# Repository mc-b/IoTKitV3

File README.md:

IoTKitV3
========

IoTKit V3 Board

- - -

Beispiele und Dokumentation zum IoTKit V3 Board. Für eine Einführung und Vertiefung in das Internet der Dinge siehe [Kurse und Weiterbildung auf Zertifikatsstufe CAS](#kurse-und-weiterbildung-auf-zertifikatsstufe-cas)

## Grundlagen

* [Hardware](hw/)
* [Software und Installation](sw/)
* [Kleine C/C++ Einführung](ccpp/)
* [GPIO](gpio/)
* [Das Konfigurationssystem (GPIO Belegungen)](config/)
* [Sensoren](sensors/)
* [Aktoren](actors/)

## Bus Systeme

* [UART](uart/)
* [I²C/TWI](i2c/)
* [SPI](spi/)

## WLAN (WiFi) / Bluetooth

* [WLAN (WiFi)](wlan/)
* [Bluetooth](bluetooth/)

### Internet IoT Protokolle

* [Sockets (TCP/UDP)](tcpip/)
* [HTTP](http/)
* [MQTT](mqtt/)
* [CoAP](coap/)

## Anwendungen

* [Cloud Dienste](cloud/) wie IFTTT, Yahoo Weather
* [LAM (Linux, Apache, MySQL) Server](LAM/)
* [Industrie V4.0](industrieV4/)
* [Roboter](roboter/)
* [NFC / RFID](rfid/)
* [Workflow](workflow/)
* [Edge Computing](edge/)
* [Built with Mbed](https://www.mbed.com/built-with-mbed/)

## Erweiterungen

Für die nachfolgenden Erweiterten Beispiele wird evtl. zusätzliche HW, wie z.B. ein Data Logging Shield, benötigt.

* [Speicher APIs](storage/)

## Kurse und Weiterbildung auf Zertifikatsstufe CAS

* [CAS Internet of Things (IoT) and Digital Ecosystem Technologien verstehen, Lösungen entwickeln](http://hslu.ch/casiot)
* [CAS Cloud and Platform Manager Mit Cloud-Expertise die Digitalisierung mitgestalten](http://hslu.ch/cascpm) 
* [Internet of Things (IoT) im Einsatz](https://www.digicomp.ch/d/IOTEIN)

## Links

* [ARM mbed](https://www.mbed.com)
* [Beispiele von Implementierungen mit mbed OS](https://www.mbed.com/built-with-mbed/)
* [mbed Labs](https://labs.mbed.com/)
* [ARM mbed YouTube Channel](https://www.youtube.com/channel/UCNcxd73dSceKtU77XWMOg8A)
* [Die drei Hauptklassen von IoT](https://www.arm.com/products/iot/soc)
* [Geschäftsmodelle und IoT](https://www.iot-lab.ch/publications/#whitepapers)
* [IoTKit Übersicht alle Versionen](https://github.com/mc-b/IoTKit#internet-der-dinge-kit)

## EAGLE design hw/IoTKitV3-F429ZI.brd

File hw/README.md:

## IoTKit V3
***

> [⇧ **Home**](../README.md)

Der Internet der Dinge Kit V3 besteht aus mehreren Boards, die mit den Beispielen verwendet werden können.

Es sind das 
* [IoTKitV3 K64F](#iotkitv3-k64f) - das eigens für das IoTKit entwickelte Board, basierend auf einen [NXP FRDM-K64F Board](https://os.mbed.com/platforms/FRDM-K64F/). 
* Ein [DISCO-L475VG-IOT01A](#DISCO-L475VG-IOT01A) Board mit einem zusätzlichen Shield, welches die fehlenden Treiber für Motoren etc. enthält.

Und zusätzliche [Komponenten](#zubehör) wie Motoren, LED Streifen, Sensoren etc.

Beide Boards können einzeln oder parallel verwendet werden.

## IoTKitV3 K64F
***

> [⇧ **Nach oben**](#)

Internet der Dinge Board

- - -

Der IoTKit ist ein [NXP FRDM-K64F Board](https://os.mbed.com/platforms/FRDM-K64F/) kompatibles Board.
 
Entstanden ist das Board durch die Kombination des [NXP FRDM-K64F Board](https://os.mbed.com/platforms/FRDM-K64F/) und einzelner Shields (z.B. Erweiterungsshield, Motorshield etc.). Dadurch sind Pin&#039;s doppelt belegt. Überall wo dies der Fall ist, kann immer nur eine Funktion gleichzeitig genutzt werden. Beispiel ist ein Gleichstrom Motor, am 2\. Anschluss angeschlossen, kann nicht gleichzeitig die MOSFET Verstärkerschaltung genutzt werden, weil sich diese die Pin&#039;s D5 - D7 teilen

* [Schaltplan](IoTKitV3.pdf) 

#### Board features

* [Bluetooth® V4.1 module (SPBTLE-RF)](../bluetooth/)
* [Proximity sensor, gesture and ambient light sensing (ALS) module (VL6180X)](../i2c#vl6180x)
* [low power, high sensitivity, RED, GREEN and BLUE color light sensor (RGB)](../i2c#ISL29125)
* [Hall Sensor](../sensors#Hall-Sensor)
* [NFC/RFID Reader](../rfid/)
* [Capacitive digital sensor for relative humidity and temperature (HTS221)](../i2c#hts221)
* [High-performance 3-axis magnetometer (LIS3MDL)](../i2c#lis3mdl)
* [3D accelerometer and 3D gyroscope (LSM6DSL)](../i2c#LSM6DSL)
* [Wi-Fi® module ESP8266](../wlan)

* OpenSDA USB Debug and Programming adapter
* Reset Button
* [SPI Header](../spi/)
* [GND/5V/Signal Arduino Pins D13 - D2](../gpio/)
* [I2C Header](../i2c/)
* [MOSFet](../actors)
* Expansion connectors: Arduino™ Uno V3
* [SWDAP](https://os.mbed.com/teams/mbed/wiki/SWDAP)
* [ARM Cortex M4 K64F MCU](https://www.nxp.com/products/processors-and-microcontrollers/arm-based-processors-and-mcus/kinetis-cortex-m-mcus/k-seriesperformancem4/k6x-ethernet/kinetis-k64-120-mhz-256kb-sram-microcontrollers-mcus-based-on-arm-cortex-m4-core:K64_120)
* [Grove Header](http://wiki.seeedstudio.com/Grove_System/)
* OLED Display
* [4 LED an GPIO D10 - D13](../gpio#DigitalOut)

* [H-Bridge](../actors/)
* [Buzzer](../gpio/)
* [Stepper Driver](../actors/)

* 12 Volt Power Supply
* Charger 5V from batt.
* [GND/5V/Signal Arduino Pins A0 - A5](../gpio/)
* [UART Header](../uart/)

* [Encoder Switch](../gpio)

## DISCO-L475VG-IOT01A
***

> [⇧ **Nach oben**](#)

Der Internet der Dinge Kit V3 Disco besteht aus den nachfolgenden Komponenten.

### Board DISCO-L475VG-IOT01A

Internet der Dinge Disco L475VG Board

- - -

* [mbed Page](https://os.mbed.com/platforms/ST-Discovery-L475E-IOT01A/)
* [Product Page](https://www.st.com/en/evaluation-tools/b-l475e-iot01a.html?icmp=tt5071_gl_bn_apr2017)
* [User Manual](https://www.st.com/content/ccc/resource/technical/document/user_manual/group0/b1/b8/7a/f2/f7/8d/4b/6b/DM00347848/files/DM00347848.pdf/jcr:content/translations/en.DM00347848.pdf)
* [Schematics](https://www.st.com/resource/en/schematic_pack/b-l475e-iot01ax_sch.zip)

#### Board features

* 64-Mbit Quad-SPI (Macronix) Flash memory
* Bluetooth® V4.1 module (SPBTLE-RF)
* Sub-GHz (868 or 915 MHz) low-power-programmable RF module (SPSGRF-868 or SPSGRF-915)
* [Wi-Fi® module Inventek ISM43362-M3G-L44 (802.11 b/g/n compliant)](../wlan)
* Dynamic NFC tag based on M24SR with its printed NFC antenna
* 2 digital omnidirectional microphones (MP34DT01)
* [Capacitive digital sensor for relative humidity and temperature (HTS221)](../i2c#HTS221)
* [High-performance 3-axis magnetometer (LIS3MDL)](../i2c#LIS3MDL)
* [3D accelerometer and 3D gyroscope (LSM6DSL)](../i2c#LSM6DSL)
* 260-1260 hPa absolute digital output barometer (LPS22HB)
* [Time-of-Flight and gesture-detection sensor (VL53L0X)](../i2c#VL53L0X)
* [2 push-buttons (user and reset)](../gpio)
* USB OTG FS with Micro-AB connector
* Expansion connectors:
* Arduino™ Uno V3
* PMOD

## NUCLEO-F303RE
***

Internet der Dinge Board Nucleo F303 RE
- - -

Das STM32 Nucleo-Board bietet Anwendern eine erschwingliche und flexible Möglichkeit, neue Ideen auszuprobieren und Prototypen zu bauen.

#### Board features

STM32F303RET6 in LQFP64 package
ARM®32-bit Cortex®-M4 CPU, 72 MHz max CPU frequency
512 KB Flash, 80 KB SRAM
GPIO (51) with external interrupt capability, 12-bit ADC (4), 12-bit DAC (2)
RTC, Timers (10)
I2C (3), USART (5), SPI (4), USB 2.0 full-speed, CAN

* [mbed Page](https://os.mbed.com/platforms/ST-Nucleo-F303RE/)

## Shield
***

Internet der Dinge Shield 

- - -

Der IoTKit V3 Shield ist ein Arduino Header kompatibler Shield.

Shield features
* 1 x SPI Header
* 1 x NFC/RFID Reader Header
* 2 x UART Header (1x Grove)
* 4 x Servo 4x3 Header
* 2 x I2C Header (1x Grove)
* 1 x Leistungsstufe für Schrittmotoren, Türöffner oder für die Ansteuerung von LED Streifen
* 1 x Hall Sensor
* 1 x OLED (128x64 Pixel)
* 1 x H-Bridge für 2 DC Motoren
* 8 x Analog/Digital 6x3 Header und 2 x Grove
* 1 x Buzzer

## Shield (small)

Internet der Dinge Shield (small)

- - -

Der IoTKit V3 Shield (small) ist die abgespeckte Variante des IoTKit Shields. 

Shield features
* 1 x SPI Header
* 1 x NFC/RFID Reader Header
* 1 x I2C Header (Grove)
* 1 x SD Card Header
* 1 x Hall Sensor
* 1 x OLED (128x64 Pixel)
* 1 x H-Bridge für 2 DC Motoren
* 4 x Analog/Digital 6x3 Header z.B. für Sensoren und Servos
* 1 x Grove
* 1 x Anschluss für BMP180 Sensor für die Messung von Luftdruck und Temperatur.
* 1 x Anschluss für APDS-9930 ein Umgebungslicht (ALS) und Näherungssensor

## Zubehör
***

> [⇧ **Nach oben**](#)

*   **Sensoren** RFID Reader (MFRC-522), PIR Sensor (SR501), Ultrasonic Wave Detector Ranging Module (HC-SR04), Digital Temperature and Humidity Sensor (DHT11), Microswitch Limit Switch: [AliExpress](http://www.aliexpress.com/), [EBay](http://www.ebay.ch/), [Conrad](http://www.conrad.ch/) (teilweise)
*   **Aktoren** 5V Stepper Motor (28BYJ-48), DC Motor, Wheels, 9g Mini Micro Servo (SG90): [AliExpress](http://www.aliexpress.com/), [EBay](http://www.ebay.ch/), [Conrad](http://www.conrad.ch/) (teilweise)
*   **LED Strip&#039;s, Matrix** Led Pixel Strip (WS2801 - Variante mit 4 Adern beachten!), Dot LED Matrix: [AliExpress](http://www.aliexpress.com/), [EBay](http://www.ebay.ch/)
*   **Modems** USB To RS232 TTL Konverterkabel: [AliExpress](http://www.aliexpress.com/), [EBay](http://www.ebay.ch/)
*   **IC&#039;s, Transistoren, Widerstände, Kabel, Stecker (Crimp) etc.** [http://www.distrelec.ch/](http://www.distrelec.ch/), [https://www.reichelt.de/](https://www.reichelt.de/), [Pusterla (Ladengeschäft in Zürich)](http://www.pusterla.ch/)

Die restlichen Teile zum Drucken, mittels 3D Drucker, sind auf [http://www.thingiverse.com/](http://www.thingiverse.com/thing:805047) zu finden. Dort befindet sich auch die Dateien um die IoTKit Box, mittels einer CNC Maschine, zu fräsen. Zum Befestigen der Teile werden 2 x M3x20 Linsenschrauben mit Muttern (Schrittmotor ), 1 x M3x30 Linsenschraube mit Mutter (Motorklammer) und zwei Drahtstife (Nägel) mit Durchmesser 1.5mm o.ä. für den Endschalter benötigt.

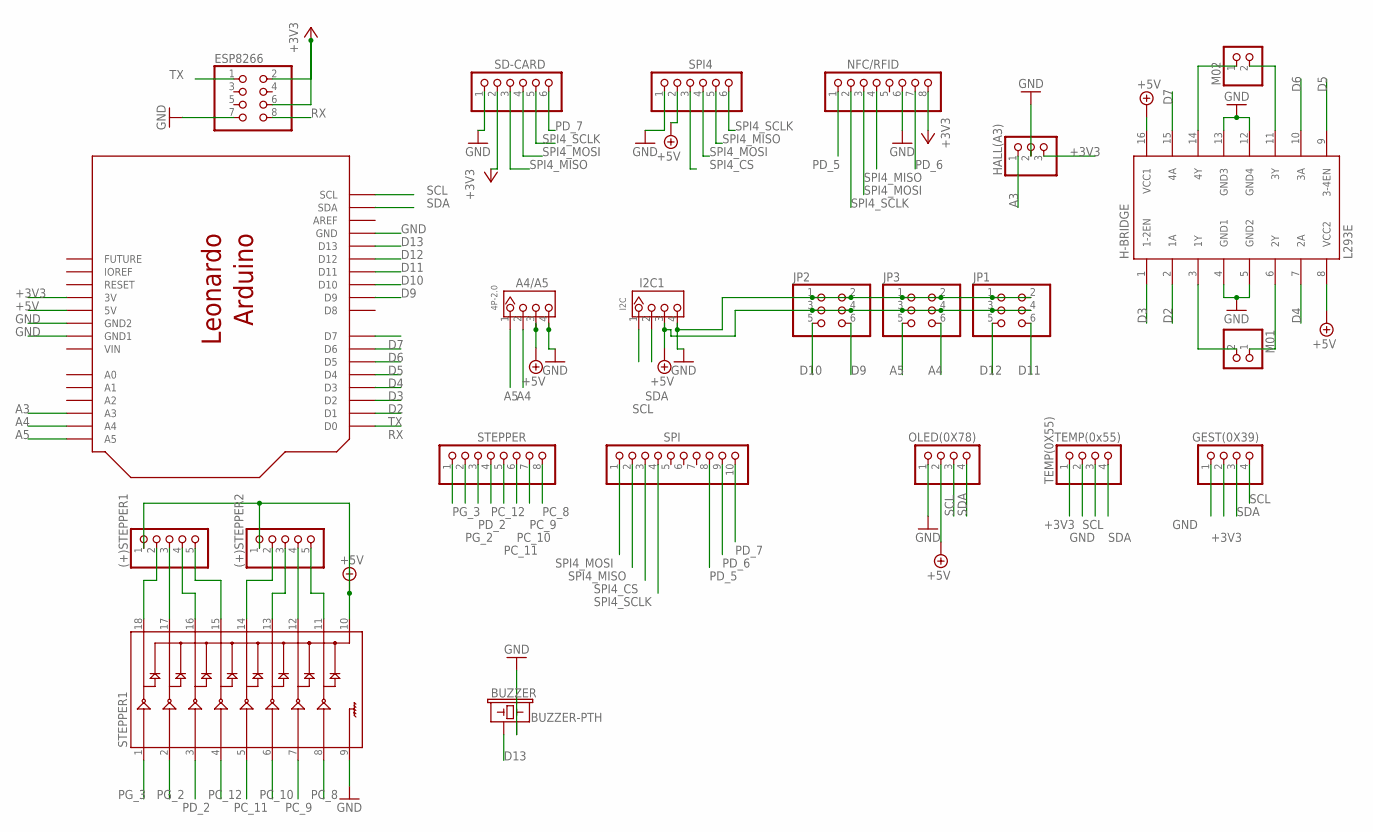
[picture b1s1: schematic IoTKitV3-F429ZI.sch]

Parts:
(+)STEPPER1, (+)STEPPER2: PINHD-1X5; 1X05
A4/A5: 4P-2.0; HW4-2.0
BUZZER: BUZZER-PTH; BUZZER-12MM
ESP8266: PINHD-2X4; 2X04
GEST(0X39): PINHD-1X4; 1X04
H-BRIDGE: L293E; DIL16
HALL(A3): PINHD-1X3; 1X03
I2C1: I2C; HW4-2.0
JP1, JP2, JP3: PINHD-2X3; 2X03
M01, M02: PINHD-1X2; 1X02
NFC/RFID: PINHD-1X8; 1X08
OLED(0X78): PINHD-1X4; 1X04
SD-CARD: PINHD-1X6; 1X06
SPI: PINHD-1X10; 1X10
SPI4: PINHD-1X6; 1X06
STEPPER: PINHD-1X8; 1X08
STEPPER1: ULN2803DIP; DIL18
TEMP(0X55): TEMP(0x55); 1X04
U$1: ARDUINO_LEONARDO

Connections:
+3V3: ESP8266.2, ESP8266.6, GEST(0X39).2, HALL(A3).3, NFC/RFID.8, SD-CARD.2, TEMP(0X55).1, U$1.3V
+5V: (+)STEPPER1.1, (+)STEPPER2.1, A4/A5.3, H-BRIDGE.8 (VCC2), H-BRIDGE.16 (VCC1), I2C1.3, JP1.3, JP1.4, JP2.3, JP2.4, JP3.3, JP3.4, OLED(0X78).2, SPI4.2, STEPPER1.10, U$1.5V
A3: HALL(A3).1, U$1.A3
A4: A4/A5.2, JP3.6, U$1.A4
A5: A4/A5.1, JP3.5, U$1.A5
D2: H-BRIDGE.2 (1A), U$1.D2
D3: H-BRIDGE.1 (1-2EN), U$1.D3
D4: H-BRIDGE.7 (2A), U$1.D4
D5: H-BRIDGE.9 (3-4EN), U$1.D5
D6: H-BRIDGE.10 (3A), U$1.D6
D7: H-BRIDGE.15 (4A), U$1.D7
D9: JP2.6, U$1.D9
D10: JP2.5, U$1.D10
D11: JP1.6, U$1.D11
D12: JP1.5, U$1.D12
D13: BUZZER.+ (1), U$1.D13
GND: A4/A5.4, BUZZER.- (2), ESP8266.7, GEST(0X39).1, H-BRIDGE.4 (GND1), H-BRIDGE.5 (GND2), H-BRIDGE.12 (GND4), H-BRIDGE.13 (GND3), HALL(A3).2, I2C1.4, JP1.1, JP1.2, JP2.1, JP2.2, JP3.1, JP3.2, NFC/RFID.6, OLED(0X78).1, SD-CARD.1, SPI4.1, STEPPER1.9, TEMP(0X55).2, U$1.GND, U$1.GND$2 (GND2), U$1.GND$3 (GND1)
M01: H-BRIDGE.6 (2Y), M01.1
unnamed: (+)STEPPER2.2, STEPPER1.14
unnamed: (+)STEPPER2.3, STEPPER1.13
unnamed: (+)STEPPER2.4, STEPPER1.12
unnamed: (+)STEPPER2.5, STEPPER1.11
unnamed: (+)STEPPER1.2, STEPPER1.18
unnamed: (+)STEPPER1.3, STEPPER1.17
unnamed: (+)STEPPER1.4, STEPPER1.16
unnamed: (+)STEPPER1.5, STEPPER1.15
unnamed: H-BRIDGE.14 (4Y), M02.1
unnamed: H-BRIDGE.11 (3Y), M02.2
unnamed: H-BRIDGE.3 (1Y), M01.2
PC_8: STEPPER.8, STEPPER1.8
PC_9: STEPPER.7, STEPPER1.7
PC_10: STEPPER.6, STEPPER1.6
PC_11: STEPPER.5, STEPPER1.5
PC_12: STEPPER.4, STEPPER1.4
PD_2: STEPPER.3, STEPPER1.3
PD_5: NFC/RFID.1, SPI.8
PD_6: NFC/RFID.7, SPI.9
PD_7: SD-CARD.6, SPI.10
PG_2: STEPPER.2, STEPPER1.2
PG_3: STEPPER.1, STEPPER1.1
RX: ESP8266.8, U$1.D0
SCL: GEST(0X39).4, I2C1.1, OLED(0X78).3, TEMP(0X55).3, U$1.SCL
SDA: GEST(0X39).3, I2C1.2, OLED(0X78).4, TEMP(0X55).4, U$1.SDA
SPI4_CS: SPI.3, SPI4.3
SPI4_MISO: NFC/RFID.4, SD-CARD.3, SPI.2, SPI4.5
SPI4_MOSI: NFC/RFID.3, SD-CARD.4, SPI.1, SPI4.4
SPI4_SCLK: NFC/RFID.2, SD-CARD.5, SPI.4, SPI4.6
TX: ESP8266.1, U$1.D1
VIN: U$1.VIN

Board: 2 copper layers, 23 parts (0 on the bottom side), 48 nets, no tracks yet.

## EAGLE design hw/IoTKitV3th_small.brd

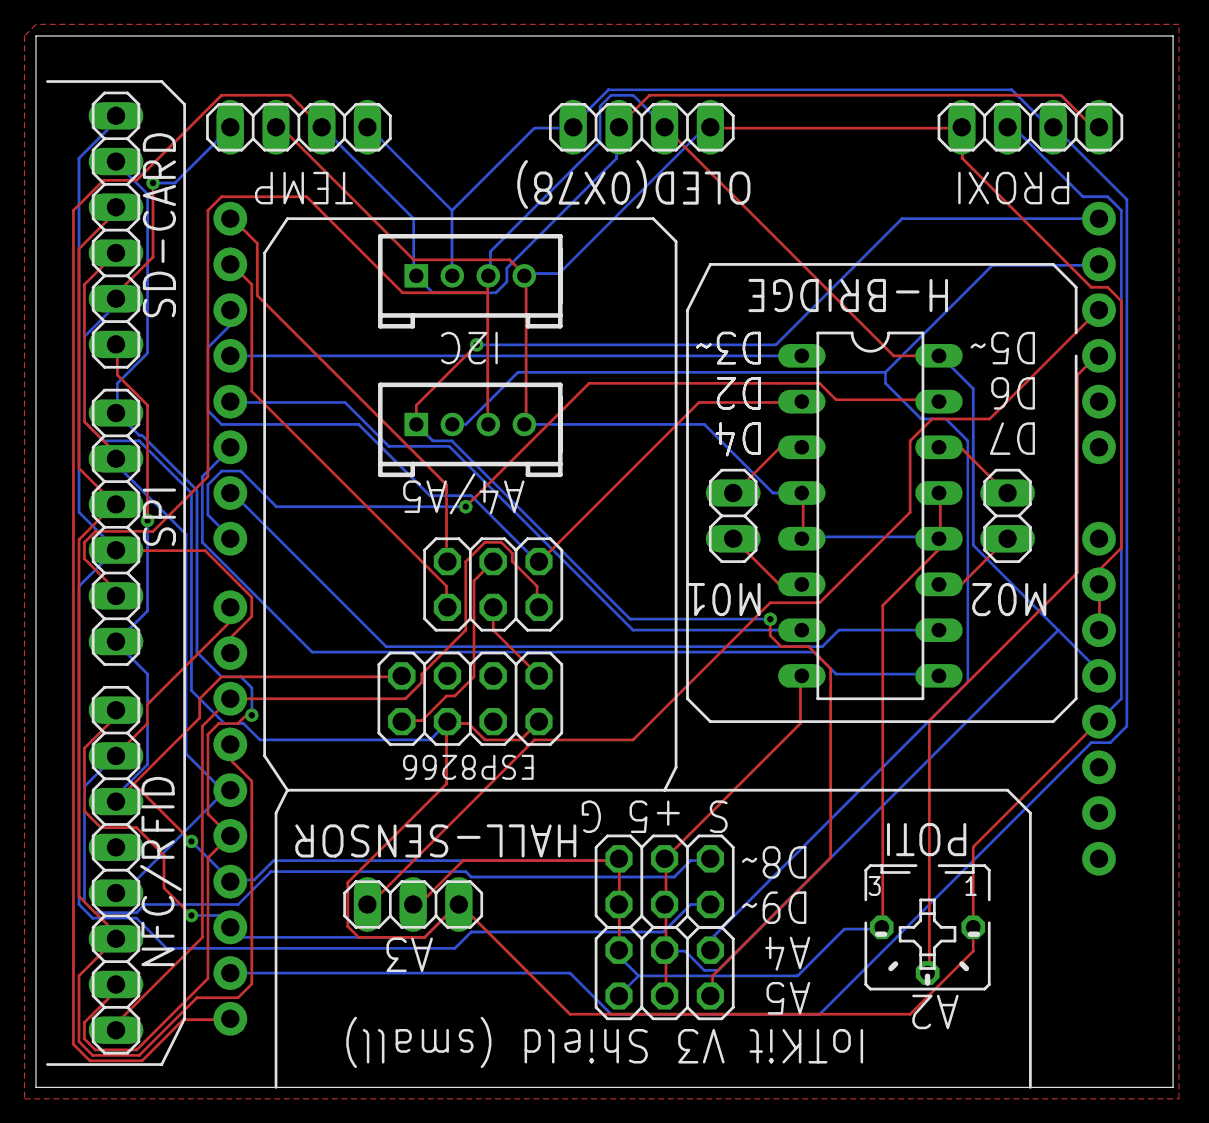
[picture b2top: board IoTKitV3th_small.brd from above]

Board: 2 copper layers, 63.2 x 58.4 mm, 18 parts (0 on the bottom side), 29 nets.

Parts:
B1: ARDUINO_UNO_R3_SHIELDNOLABELS; UNO_R3_SHIELD_NOLABELS
ESP8266: 2X04
H-BRIDGE: L293E; DIL16
HALL-SENSOR: 1X03
I2C: 4P-2.0; HW4-2.0
I2C1: I2C; HW4-2.0
JP1, JP2, JP3: 2X03
M01, M02: 1X02
NFC/RFID: 1X08
OLED(0X78): 1X04
POTI: B25P
PROXI: 1X04
SD-CARD: 1X06
SPI: 1X06
TEMP: TEMP; 1X04

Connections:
+3V3: B1.3.3V, B1.AREF, ESP8266.2, ESP8266.6, HALL-SENSOR.3, NFC/RFID.8, POTI.A, PROXI.2, SD-CARD.2, TEMP.1
+5V: B1.5V, H-BRIDGE.8, H-BRIDGE.16, I2C.3, I2C1.3, JP2.3, JP2.4, JP3.3, JP3.4, OLED(0X78).2, SPI.2
A2: B1.A2, POTI.S
A3: B1.A3, HALL-SENSOR.1
A4: B1.A4, I2C.2, JP3.6
A5: B1.A5, I2C.1, JP3.5
D2: B1.D2, H-BRIDGE.2, JP1.6
D3: B1.D3, H-BRIDGE.1
D4: B1.D4, H-BRIDGE.7
D5: B1.D5, H-BRIDGE.9
D6: B1.D6, H-BRIDGE.10
D7: B1.D7, H-BRIDGE.15
D8: B1.D8, JP2.6, NFC/RFID.7
D9: B1.D9, JP2.5, SD-CARD.6, SPI.3
D10: B1.D10, JP1.5, NFC/RFID.1
D11: B1.D11, NFC/RFID.3, SD-CARD.4, SPI.4
D12: B1.D12, NFC/RFID.4, SD-CARD.3, SPI.5
D13: B1.D13, NFC/RFID.2, SD-CARD.5, SPI.6
GND: B1.GND@0, B1.GND@1, B1.GND@2, ESP8266.7, H-BRIDGE.4, H-BRIDGE.5, H-BRIDGE.12, H-BRIDGE.13, HALL-SENSOR.2, I2C.4, I2C1.4, JP2.1, JP2.2, JP3.1, JP3.2, NFC/RFID.6, OLED(0X78).1, POTI.E, PROXI.1, SD-CARD.1, SPI.1, TEMP.2
M01: H-BRIDGE.6, M01.1
unnamed: ESP8266.1, JP1.3
unnamed: ESP8266.8, JP1.4
unnamed: H-BRIDGE.14, M02.1
unnamed: H-BRIDGE.11, M02.2
unnamed: H-BRIDGE.3, M01.2
RX: B1.RX, JP1.2
SCL: B1.SCL, I2C1.1, OLED(0X78).3, PROXI.4, TEMP.3
SDA: B1.SDA, I2C1.2, OLED(0X78).4, PROXI.3, TEMP.4
TX: B1.TX, JP1.1

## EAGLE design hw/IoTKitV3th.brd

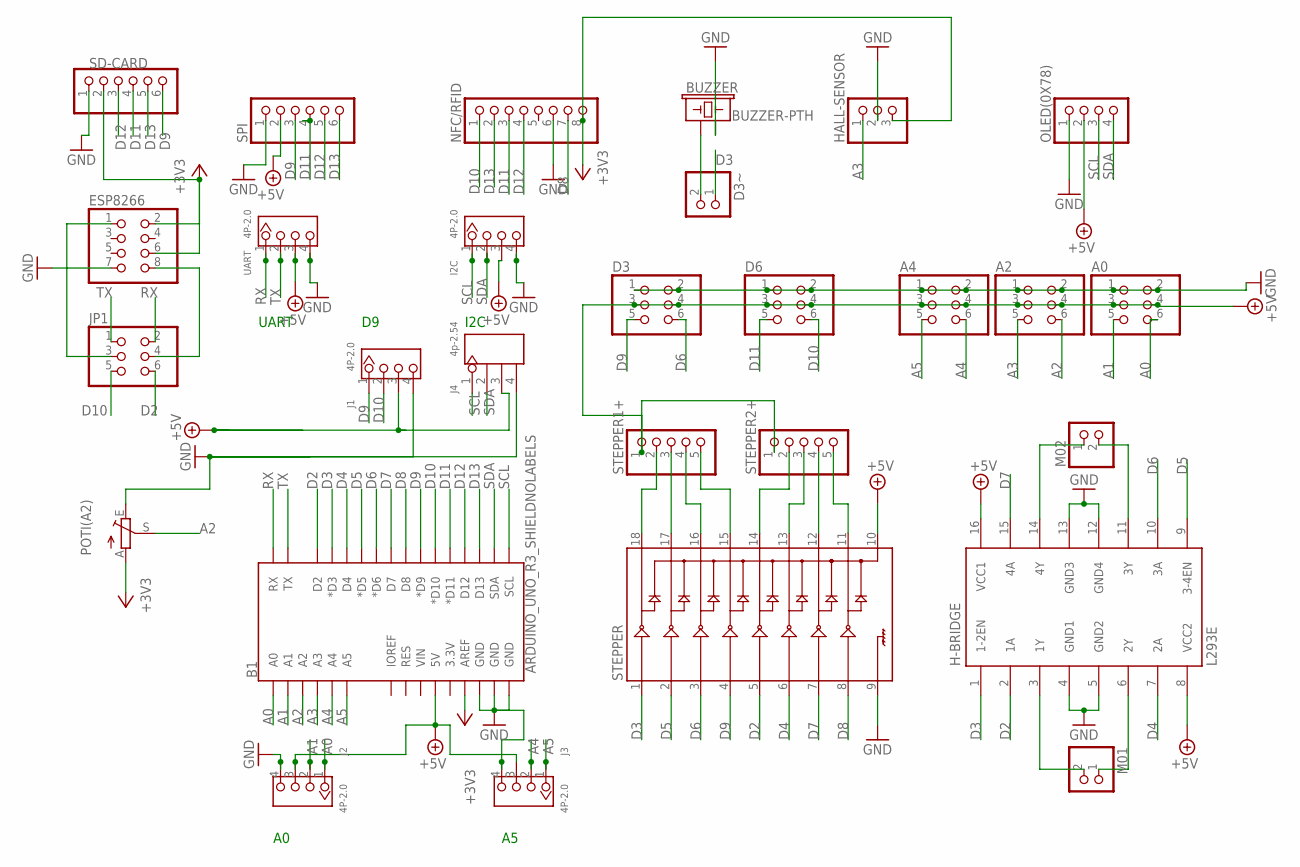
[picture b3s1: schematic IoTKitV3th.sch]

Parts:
A0, A2, A4: PINHD-2X3; 2X03
B1: ARDUINO_UNO_R3_SHIELDNOLABELS; UNO_R3_SHIELD_NOLABELS
BUZZER: BUZZER-PTH; BUZZER-12MM
D3, D6: PINHD-2X3; 2X03
D3~: PINHD-1X2; 1X02
ESP8266: PINHD-2X4; 2X04
H-BRIDGE: L293E; DIL16
HALL-SENSOR: PINHD-1X3; 1X03
I2C: 4P-2.0; HW4-2.0
J1, J2, J3: 4P-2.0; HW4-2.0
J4: 4p-2.54; H4-2.54
JP1: PINHD-2X3; 2X03
M01, M02: PINHD-1X2; 1X02
NFC/RFID: PINHD-1X8; 1X08
OLED(0X78): PINHD-1X4; 1X04
POTI(A2): TRIM_EU-B25P; B25P
SD-CARD: PINHD-1X6; 1X06
SPI: PINHD-1X6; 1X06
STEPPER: ULN2803DIP; DIL18
STEPPER1+, STEPPER2+: PINHD-1X5; 1X05
UART: 4P-2.0; HW4-2.0

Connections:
+3V3: B1.AREF, ESP8266.2, ESP8266.6, HALL-SENSOR.3, NFC/RFID.8, POTI(A2).A, SD-CARD.2
+5V: A0.3, A0.4, A2.3, A2.4, A4.3, A4.4, B1.5V, D3.3, D3.4, D6.3, D6.4, H-BRIDGE.8 (VCC2), H-BRIDGE.16 (VCC1), I2C.3, J1.3, J2.3, J3.3, J4.3, OLED(0X78).2, SPI.2, STEPPER.10, STEPPER1+.1, STEPPER2+.1, UART.3
A0: A0.6, B1.A0, J2.1
A1: A0.5, B1.A1, J2.2
A2: A2.6, B1.A2, POTI(A2).S
A3: A2.5, B1.A3, HALL-SENSOR.1
A4: A4.6, B1.A4, J3.2
A5: A4.5, B1.A5, J3.1
D2: B1.D2, H-BRIDGE.2 (1A), JP1.6, STEPPER.5
D3: B1.D3 (*D3), D3~.1, H-BRIDGE.1 (1-2EN), STEPPER.1
D4: B1.D4, H-BRIDGE.7 (2A), STEPPER.6
D5: B1.D5 (*D5), H-BRIDGE.9 (3-4EN), STEPPER.2
D6: B1.D6 (*D6), D3.6, H-BRIDGE.10 (3A), STEPPER.3
D7: B1.D7, H-BRIDGE.15 (4A), STEPPER.7
D8: B1.D8, NFC/RFID.7, STEPPER.8
D9: B1.D9 (*D9), D3.5, J1.1, SD-CARD.6, SPI.3, STEPPER.4
D10: B1.D10 (*D10), D6.6, J1.2, JP1.5, NFC/RFID.1
D11: B1.D11 (*D11), D6.5, NFC/RFID.3, SD-CARD.4, SPI.4
D12: B1.D12, NFC/RFID.4, SD-CARD.3, SPI.5
D13: B1.D13, NFC/RFID.2, SD-CARD.5, SPI.6
GND: A0.1, A0.2, A2.1, A2.2, A4.1, A4.2, B1.GND@0 (GND), B1.GND@1 (GND), B1.GND@2 (GND), BUZZER.- (2), D3.1, D3.2, D6.1, D6.2, ESP8266.7, H-BRIDGE.4 (GND1), H-BRIDGE.5 (GND2), H-BRIDGE.12 (GND4), H-BRIDGE.13 (GND3), HALL-SENSOR.2, I2C.4, J1.4, J2.4, J3.4, J4.4, NFC/RFID.6, OLED(0X78).1, POTI(A2).E, SD-CARD.1, SPI.1, STEPPER.9, UART.4
M01: H-BRIDGE.6 (2Y), M01.1
unnamed: STEPPER.14, STEPPER2+.2
unnamed: STEPPER.13, STEPPER2+.3
unnamed: STEPPER.12, STEPPER2+.4
unnamed: STEPPER.11, STEPPER2+.5
unnamed: BUZZER.+ (1), D3~.2
unnamed: ESP8266.1, JP1.3
unnamed: ESP8266.8, JP1.4
unnamed: STEPPER.18, STEPPER1+.2
unnamed: STEPPER.17, STEPPER1+.3
unnamed: STEPPER.16, STEPPER1+.4
unnamed: STEPPER.15, STEPPER1+.5
unnamed: H-BRIDGE.14 (4Y), M02.1
unnamed: H-BRIDGE.11 (3Y), M02.2
unnamed: H-BRIDGE.3 (1Y), M01.2
RX: B1.RX, JP1.2, UART.1
SCL: B1.SCL, I2C.1, J4.1, OLED(0X78).3
SDA: B1.SDA, I2C.2, J4.2, OLED(0X78).4
TX: B1.TX, JP1.1, UART.2

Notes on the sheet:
UART
I2C

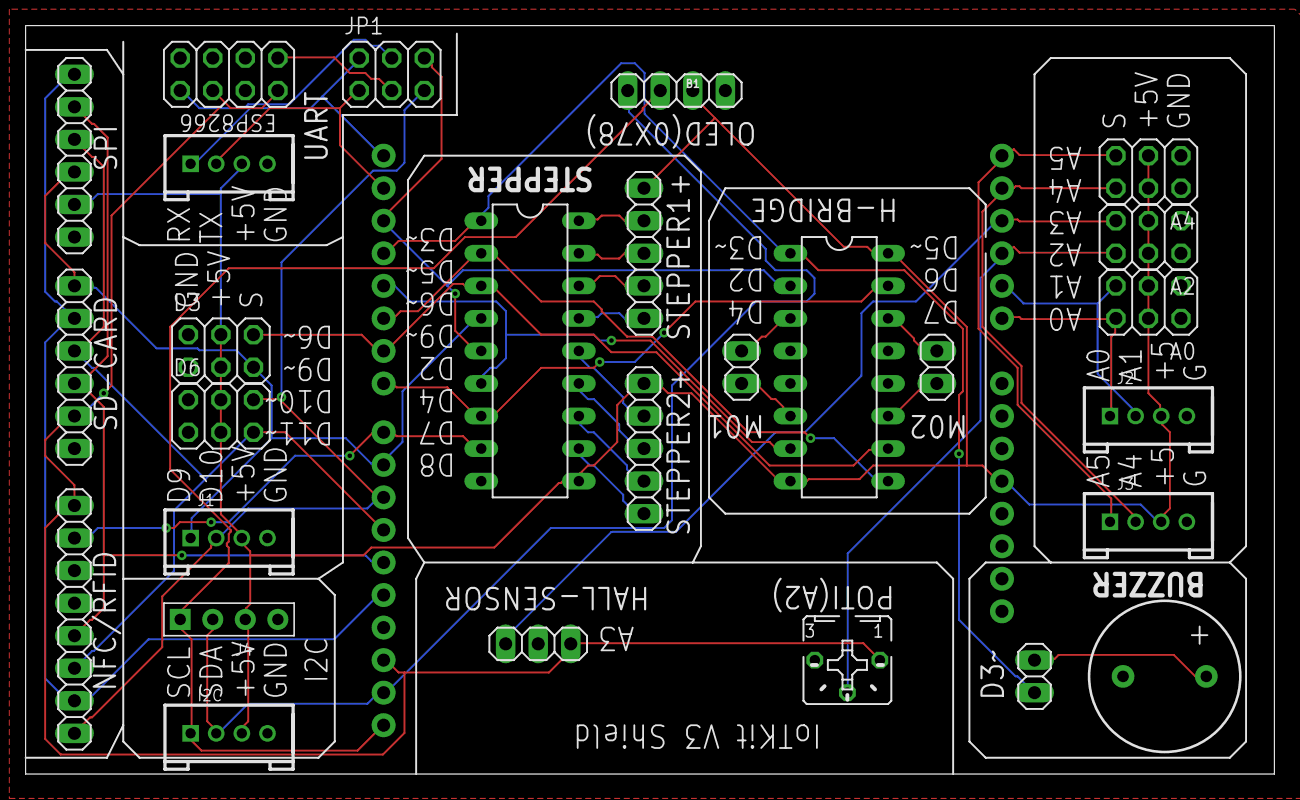
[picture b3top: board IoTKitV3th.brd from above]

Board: 2 copper layers, 97.5 x 58.4 mm, 28 parts (0 on the bottom side), 40 nets.

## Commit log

2017-08-30 Initial Commit - nicht angepasst an IoTKit V3
2017-08-30 D9 statt D7, weil D7 ein PWM Pin
2017-08-30 Umbau auf User-Button und LED1
2017-08-31 Angepasst an DISCO-L475VG-IOT
2017-08-31 Eclipse Dateien
2017-08-31 D1/D0 und USBTX/USBRX sind unterschiedliche Pin's
2017-08-31 Obsolet
2017-08-31 The BSP driver for the B-L475E-IOT01 board.
2017-08-31 Beispiel Magnetometer auf Board
2017-08-31 Link
2017-09-01 Magnetometer Beschreibung
2017-09-01 Umbau mbed OS V5.x
2018-09-08 Umgestellt auf FRMD K64F kompatibles Board
2018-09-08 Erweiterungen VSCode und PlatformIO
2018-09-08 Obsolet durch lernkube und duk
2018-09-08 Obsolet bzw. in mbed V5 nicht mehr unterstuetzt
2018-09-08 Umbau auf IoTKit V3
2018-09-08 SW Installation und Einsatz
2018-09-08 Doku
2018-09-08 Abgestimmt mit VSCode
2018-09-08 Libraries
2018-09-08 Khz Angabe
2018-09-08 Angepasst an IoTKit V3
2018-09-08 Update auf IoTKit V3
2018-09-09 Easy Connect Library
2018-09-09 RFID Library
2018-09-09 Wifi Beispiel
2018-09-09 MQTT
2018-09-09 no workspace
2018-10-04 Entwicklungsumgebungen
2018-10-04 Ueberarbeitet
2018-10-04 Ueberarbeitung
2018-10-04 BUILD ausschliessen
2018-10-04 Servo mbed OS V5 konform ansprechen
2018-10-04 Anpassen an mbed OS V5
2018-10-05 mbed OS V5
2018-10-05 mbed-cli Installation
2018-10-05 Display Test
2018-10-06 Update EPS8266 Beschreibung
2018-10-06 mbed?
2018-10-06 FAIL.TXT
2018-10-06 Board features
2018-10-06 Encoder Switch
2018-10-06 Links
2018-10-06 VL6180X
2018-10-06 ISL29125 - low power, high sensitivity, RED, GREEN and BLUE color light sensor
2018-10-06 HTS221
2018-10-06 LIS3MDL
2018-10-06 LSM6DSL
2018-10-06 NTP Beispiel
2018-10-07 HTTP Libraries und Beispiel
2018-10-07 IoTKit V3 Template
2018-10-07 PlatformIO entfernt, mbed OS Version ist zu alt
2018-10-07 CoAP Beispiel
2018-10-07 Umbau Bluetooth
2018-10-07 Einleitung
2018-11-14 C/C++ Einfuehrung
2018-11-16 Korrekturen
2018-11-28 printf, scanf Links
2018-12-04 Umbau mbed OS 5.10
2019-02-04 Mehr Kommentar
2019-02-04 Link Beispiel
2019-02-04 Kommentar ergaenzt
2019-02-04 Beschreibung
2019-02-05 Update mbed OS fuer WLAN
2019-02-12 IFTTT Beschreibung nachgefuehrt
2019-02-12 Built with Mbed
2019-02-18 ntp-client entfernt, gibt Probleme
2019-02-18 Link korr.
2019-02-18 Fehlerhafte Library entfernt
2019-02-25 Falsches Board
2019-02-25 Falscher Wertabfrage
2019-02-26 ThingSpeak Beispiel
2019-03-02 Mehr Beispiele portiert
2019-03-07 Angepasstes Beispiel an IoTKitV3
2019-03-15 Workflow Update auf neuste Beispiele
2019-03-20 Umstellung mbed OS5
2019-03-20 Bluetooth Beispiel inkl. Library
2019-03-21 Mehr Links
2019-03-23 mbed-cli Installation Ueberarbeitet
2019-03-23 Feintuning
2019-03-24 Beacon Beispiel
2019-03-27 Storage
2019-03-27 C++ Einstellungen fuer Eclipse inkl. GCC ARM Paths
2019-03-27 Buildet aktuelles Verzeichnis
2019-03-30 gibt Probleme beim compilieren. mbed_app.json aus template verwenden
2019-04-11 Link auf Beispielprogramm
2019-04-11 Ueberarbeitet und Erweitert um Button und Encoder Infos
2019-04-13 Falsches Format
2019-04-15 RFID Reader integriert
2019-04-17 6D Ausgabe
2019-04-17 Restliche Beispiele fuer Acc/Gyro
2019-04-17 Falscher Link
2019-04-20 Magnet und eCompass Abhandlung
2019-04-20 Typo
2019-04-21 Aufgeraeumt
2019-04-23 Umbau Symbolische Bezeichner - Doku kompakter
2019-04-23 Tabelle
2019-04-23 u.s.b.
2019-04-23 Beispiel AnalogIn
2019-04-23 Encoder
2019-04-23 Uebungen
2019-04-23 Abgleich
2019-04-23 Umbau auf Symbolische Bezeichner
2019-04-23 Doku ueberarbeitet
2019-04-23 Klarstellungen
2019-04-23 + 2 Uebungen
2019-04-23 Konfig
2019-04-23 Doku umbau
2019-04-23 Doku komprimiert
2019-04-23 Syntax
2019-04-23 SW Installation abgestimmt
2019-04-23 Serielle Kommunikation
2019-04-23 Kombination Boards
2019-04-24 Boards zusammengefasst
2019-04-24 Multi Board
2019-04-24 Multi Boards
2019-04-24 Umbau
2019-04-24 Doku Redesing
2019-04-24 Doku Redesign
2019-04-25 Neues Beispiel und Doku Redesign RFID
2019-04-25 Formatierung
2019-04-25 printf und scanf Beispiel
2019-04-25 NTP Online Beispiel
2019-04-25 Dokue Redesign
2019-04-25 Konfigurationssystem
2019-04-25 Ausgabe Details
2019-04-25 Home
2019-04-25 RFID und Encoder entfernt beim DISCO_L475VG_IOT01A, WLAN Modem haengt
2019-04-26 Temperatur Sensor Extern integriert
2019-04-26 Temperatur Sensor extern
2019-04-26 IoTKit Macros
2019-04-27 Feinschliff
2019-04-27 Link Kurse
2019-04-27 Einfuehrungsvideo
2019-04-30 Blog MQTT Library
2019-05-08 Doppelbelegung Disco Board von D3, Motor auf M02 verschoben
2019-05-12 Nucleo Board integriert in Build
2019-05-19 V1.1 inkl. SD Card, Poti, ESP8266, Schrift gekehrt
2019-05-19 Microbit - Arduino Adapter
2019-05-24 Unterstuetzung weitere Boards
2019-05-24 TARGET_NUCLEO_F746ZG
2019-05-25 XML Parser Library
2019-05-25 Fehlende Library und doppelte Globale Variable
2019-05-25 Unnoetige Variable
2019-05-25 Namenskonflikte
2019-05-25 Pin belegungen ESP8266
2019-05-25 Umbau Servo Library
2019-05-25 Angepasst neuste Servo Library
2019-09-01 Quellenangabe HiveMQ
2019-09-01 Quellenangabe
2020-01-12 Edge Anfang
2020-01-13 Neuste Kurse und CAS
2020-01-13 Feinausarbeitung
2020-01-13 Struktur
2020-01-15 Edge ausgearbeitet
2020-01-18 Node-RED Edge Beispiele
2020-01-18 Bilder
2020-01-19 Verbunden mit iotkit.mc-b.ch
2020-01-23 Camunda Installation
2020-01-23 REST BPMN Beispiel
2020-01-30 veraltete HW, nicht zielfuehrend - entfernt
2020-01-30 Korrektur SD Karten belegung
2020-01-30 Copyright
2020-01-30 ohne routes
2020-01-30 Verdrated
2020-02-11 Installation Board
2020-02-17 mbed-cli broken
2020-02-21 aktualisierte Gerber Files (in Test)
2020-02-21 Library Link aktualisiert
2020-02-24 Korrektur mehrere RFID Tags
2020-03-02 IFTTT Alternatives
2020-03-07 Storage aktualisiert
2020-03-08 Grove und Servo Anschluesse
2020-03-08 R1.0
2020-03-08 R1.1
2020-03-08 R1.1 Gerber
2020-03-22 LAM Server
2020-03-23 Update rest
2020-04-05 Korrektur Output Anzeige
2020-04-05 Output a String
2020-04-16 V1.2 mit MEMS Temp und Proxi Sensoren
2020-05-25 F303RE Board
2020-05-25 Einbau Nucleo F303RE Board und IoTKit V3 small
2020-05-27 DOTLED Pin
2020-05-29 Edge Umgebung fuer Raspberry Pi 4 mit k3s
2020-05-29 Raspi 4
2020-05-30 BMP180 Temp / Pressure Sensor
2020-05-30 Datenblatt
2021-01-13 Optimierungen SPI, SD Card Adapter, APDS-9960 statt 9930
2021-02-25 ADPS9960 statt ADPS9930
2021-04-05 IoTKit V3 V1.3 Shield fuer NUCLEO-F429ZI
2021-05-30 IoTKitV3 1.3 F429ZI Schema
2021-08-10 test
2025-04-24 backstage.io

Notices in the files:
parts and their libraries:
SparkFun-IC-Special-Function: Licensing: Creative Commons ShareAlike 4.0 International - https://creativecommons.org/licenses/by-sa/4.0
